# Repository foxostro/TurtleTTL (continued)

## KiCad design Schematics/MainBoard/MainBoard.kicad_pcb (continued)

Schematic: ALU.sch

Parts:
C74, C75, C76, C77: 100nF; C_Disc_D4.3mm_W1.9mm_P5.00mm
D3, D4: LED; LED_D5.0mm
J10: ALU Result LED Connector; PinSocket_1x09_P2.54mm_Vertical
R28, R29: 220Ω; R_Axial_DIN0207_L6.3mm_D2.5mm_P7.62mm_Horizontal
R38: 4.7kΩ; R_Axial_DIN0207_L6.3mm_D2.5mm_P7.62mm_Horizontal
U69, U70: 74F181; DIP-24_W15.24mm_Socket
U71: 74LS245; DIP-20_W7.62mm_Socket
U72: 74F377; DIP-20_W7.62mm

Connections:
/ALU/A=B: R38.2, U69.14 (A=B), U70.14 (A=B), U72.4 (D1)
/ALU/AluResult0: J10.2, U69.9 (F0), U71.2 (A0)
/ALU/AluResult1: J10.3, U69.10 (F1), U71.3 (A1)
/ALU/AluResult2: J10.4, U69.11 (F2), U71.4 (A2)
/ALU/AluResult3: J10.5, U69.13 (F3), U71.5 (A3)
/ALU/AluResult4: J10.6, U70.9 (F0), U71.6 (A4)
/ALU/AluResult5: J10.7, U70.10 (F1), U71.7 (A5)
/ALU/AluResult6: J10.8, U70.11 (F2), U71.8 (A6)
/ALU/AluResult7: J10.9, U70.13 (F3), U71.9 (A7)
/ALU/Cn+4: U70.16 (Cn+4), U72.3 (D0)
A0: U69.2 (A0); also elsewhere on the board
A1: U69.23 (A1); also elsewhere on the board
A2: U69.21 (A2); also elsewhere on the board
A3: U69.19 (A3); also elsewhere on the board
A4: U70.2 (A0); also elsewhere on the board
A5: U70.23 (A1); also elsewhere on the board
A6: U70.21 (A2); also elsewhere on the board
A7: U70.19 (A3); also elsewhere on the board
B0: U69.1 (B0); also elsewhere on the board
B1: U69.22 (B1); also elsewhere on the board
B2: U69.20 (B2); also elsewhere on the board
B3: U69.18 (B3); also elsewhere on the board
B4: U70.1 (B0); also elsewhere on the board
B5: U70.22 (B1); also elsewhere on the board
B6: U70.20 (B2); also elsewhere on the board
B7: U70.18 (B3); also elsewhere on the board
C0: U69.6 (S0), U70.6 (S0); also elsewhere on the board
C1: U69.5 (S1), U70.5 (S1); also elsewhere on the board
C2: U69.4 (S2), U70.4 (S2); also elsewhere on the board
C3: U69.3 (S3), U70.3 (S3); also elsewhere on the board
C4: U69.7 (Cn); also elsewhere on the board
C5: U69.8 (M), U70.8 (M); also elsewhere on the board
DataBus0: U71.18 (B0); also elsewhere on the board
DataBus1: U71.17 (B1); also elsewhere on the board
DataBus2: U71.16 (B2); also elsewhere on the board
DataBus3: U71.15 (B3); also elsewhere on the board
DataBus4: U71.14 (B4); also elsewhere on the board
DataBus5: U71.13 (B5); also elsewhere on the board
DataBus6: U71.12 (B6); also elsewhere on the board
DataBus7: U71.11 (B7); also elsewhere on the board
GND: C74.2, C75.2, C76.2, C77.2, J10.1, R28.2, R29.2, U69.12 (GND), U70.12 (GND), U71.10 (GND), U72.10 (GND); also elsewhere on the board
unnamed: D3.1 (K), R28.1
unnamed: D4.1 (K), R29.1
unnamed: U69.16 (Cn+4), U70.7 (Cn)
RegisterClock: U72.11 (CP); also elsewhere on the board
VCC: C74.1, C75.1, C76.1, C77.1, R38.1, U69.24 (VCC), U70.24 (VCC), U71.1 (A->B), U71.20 (VCC), U72.20 (VCC); also elsewhere on the board
~A=B: D4.2 (A), U72.5 (Q1); also elsewhere on the board
~CarryOut: D3.2 (A), U72.2 (Q0); also elsewhere on the board
~EO: U71.19 (CE); also elsewhere on the board
~FI: U72.1 (~E); also elsewhere on the board

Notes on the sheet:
Flags Register

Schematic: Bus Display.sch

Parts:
J11: Address Bus LED Connector; PinSocket_1x17_P2.54mm_Vertical
J12: Data Bus LED Connector; PinSocket_1x09_P2.54mm_Vertical
RN1: 1kΩ; R_Array_SIP9

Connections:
AddressBus0: J11.2; also elsewhere on the board
AddressBus1: J11.3; also elsewhere on the board
AddressBus2: J11.4; also elsewhere on the board
AddressBus3: J11.5; also elsewhere on the board
AddressBus4: J11.6; also elsewhere on the board
AddressBus5: J11.7; also elsewhere on the board
AddressBus6: J11.8; also elsewhere on the board
AddressBus7: J11.9; also elsewhere on the board
AddressBus8: J11.10; also elsewhere on the board
AddressBus9: J11.11; also elsewhere on the board
AddressBus10: J11.12; also elsewhere on the board
AddressBus11: J11.13; also elsewhere on the board
AddressBus12: J11.14; also elsewhere on the board
AddressBus13: J11.15; also elsewhere on the board
AddressBus14: J11.16; also elsewhere on the board
AddressBus15: J11.17; also elsewhere on the board
DataBus0: J12.2, RN1.2 (R1); also elsewhere on the board
DataBus1: J12.3, RN1.3 (R2); also elsewhere on the board
DataBus2: J12.4, RN1.4 (R3); also elsewhere on the board
DataBus3: J12.5, RN1.5 (R4); also elsewhere on the board
DataBus4: J12.6, RN1.6 (R5); also elsewhere on the board
DataBus5: J12.7, RN1.7 (R6); also elsewhere on the board
DataBus6: J12.8, RN1.8 (R7); also elsewhere on the board
DataBus7: J12.9, RN1.9 (R8); also elsewhere on the board
GND: J11.1, J12.1, RN1.1 (common); also elsewhere on the board

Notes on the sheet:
Data Bus Pull-down Resistors

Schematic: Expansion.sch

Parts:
J17: Device 2; PinSocket_2x20_P2.54mm_Vertical
J18: Device 5; PinSocket_2x20_P2.54mm_Vertical
J19: Device 3; PinSocket_2x20_P2.54mm_Vertical
J20: Device 6; PinSocket_2x20_P2.54mm_Vertical
J21: Device 4; PinSocket_2x20_P2.54mm_Vertical
J22: Device 7; PinSocket_2x20_P2.54mm_Vertical

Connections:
AddressBus0: J17.3, J18.3, J19.3, J20.3, J21.3, J22.3; also elsewhere on the board
AddressBus1: J17.4, J18.4, J19.4, J20.4, J21.4, J22.4; also elsewhere on the board
AddressBus2: J17.5, J18.5, J19.5, J20.5, J21.5, J22.5; also elsewhere on the board
AddressBus3: J17.6, J18.6, J19.6, J20.6, J21.6, J22.6; also elsewhere on the board
AddressBus4: J17.7, J18.7, J19.7, J20.7, J21.7, J22.7; also elsewhere on the board
AddressBus5: J17.8, J18.8, J19.8, J20.8, J21.8, J22.8; also elsewhere on the board
AddressBus6: J17.9, J18.9, J19.9, J20.9, J21.9, J22.9; also elsewhere on the board
AddressBus7: J17.10, J18.10, J19.10, J20.10, J21.10, J22.10; also elsewhere on the board
AddressBus8: J17.11, J18.11, J19.11, J20.11, J21.11, J22.11; also elsewhere on the board
AddressBus9: J17.12, J18.12, J19.12, J20.12, J21.12, J22.12; also elsewhere on the board
AddressBus10: J17.13, J18.13, J19.13, J20.13, J21.13, J22.13; also elsewhere on the board
AddressBus11: J17.14, J18.14, J19.14, J20.14, J21.14, J22.14; also elsewhere on the board
AddressBus12: J17.15, J18.15, J19.15, J20.15, J21.15, J22.15; also elsewhere on the board
AddressBus13: J17.16, J18.16, J19.16, J20.16, J21.16, J22.16; also elsewhere on the board
AddressBus14: J17.17, J18.17, J19.17, J20.17, J21.17, J22.17; also elsewhere on the board
AddressBus15: J17.18, J18.18, J19.18, J20.18, J21.18, J22.18; also elsewhere on the board
DataBus0: J17.21, J18.21, J19.21, J20.21, J21.21, J22.21; also elsewhere on the board
DataBus1: J17.22, J18.22, J19.22, J20.22, J21.22, J22.22; also elsewhere on the board
DataBus2: J17.23, J18.23, J19.23, J20.23, J21.23, J22.23; also elsewhere on the board
DataBus3: J17.24, J18.24, J19.24, J20.24, J21.24, J22.24; also elsewhere on the board
DataBus4: J17.25, J18.25, J19.25, J20.25, J21.25, J22.25; also elsewhere on the board
DataBus5: J17.26, J18.26, J19.26, J20.26, J21.26, J22.26; also elsewhere on the board
DataBus6: J17.27, J18.27, J19.27, J20.27, J21.27, J22.27; also elsewhere on the board
DataBus7: J17.28, J18.28, J19.28, J20.28, J21.28, J22.28; also elsewhere on the board
FixedRateClock: J17.20, J18.20, J19.20, J20.20, J21.20, J22.20; also elsewhere on the board
GND: J17.1, J17.31, J17.32, J17.33, J17.34, J17.35, J17.36, J17.37, J17.38, J17.39, J17.40, J18.1, J18.31, J18.32, J18.33, J18.34, J18.35, J18.36, J18.37, J18.38, J18.39, J18.40, J19.1, J19.31, J19.32, J19.33, J19.34, J19.35, J19.36, J19.37, J19.38, J19.39, J19.40, J20.1, J20.31, J20.32, J20.33, J20.34, J20.35, J20.36, J20.37, J20.38, J20.39, J20.40, J21.1, J21.31, J21.32, J21.33, J21.34, J21.35, J21.36, J21.37, J21.38, J21.39, J21.40, J22.1, J22.31, J22.32, J22.33, J22.34, J22.35, J22.36, J22.37, J22.38, J22.39, J22.40; also elsewhere on the board
RegisterClock: J17.19, J18.19, J19.19, J20.19, J21.19, J22.19; also elsewhere on the board
VCC: J17.2, J18.2, J19.2, J20.2, J21.2, J22.2; also elsewhere on the board
~PI2: J17.29; also elsewhere on the board
~PI3: J19.29; also elsewhere on the board
~PI4: J21.29; also elsewhere on the board
~PI5: J18.29; also elsewhere on the board
~PI6: J20.29; also elsewhere on the board
~PI7: J22.29; also elsewhere on the board
~PO2: J17.30; also elsewhere on the board
~PO3: J19.30; also elsewhere on the board
~PO4: J21.30; also elsewhere on the board
~PO5: J18.30; also elsewhere on the board
~PO6: J20.30; also elsewhere on the board
~PO7: J22.30; also elsewhere on the board

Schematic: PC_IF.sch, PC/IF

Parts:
C22, C23: 100nF; C_Disc_D4.3mm_W1.9mm_P5.00mm
U22, U23: 74F574; DIP-20_W7.62mm

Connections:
ControlClock: U22.11 (Cp), U23.11 (Cp); also elsewhere on the board
GND: C22.2, C23.2, U22.1 (OE), U22.10 (GND), U23.1 (OE), U23.10 (GND); also elsewhere on the board
PC0: U22.2 (D0); also elsewhere on the board
PC1: U22.3 (D1); also elsewhere on the board
PC2: U22.4 (D2); also elsewhere on the board
PC3: U22.5 (D3); also elsewhere on the board
PC4: U22.6 (D4); also elsewhere on the board
PC5: U22.7 (D5); also elsewhere on the board
PC6: U22.8 (D6); also elsewhere on the board
PC7: U22.9 (D7); also elsewhere on the board
PC8: U23.2 (D0); also elsewhere on the board
PC9: U23.3 (D1); also elsewhere on the board
PC10: U23.4 (D2); also elsewhere on the board
PC11: U23.5 (D3); also elsewhere on the board
PC12: U23.6 (D4); also elsewhere on the board
PC13: U23.7 (D5); also elsewhere on the board
PC14: U23.8 (D6); also elsewhere on the board
PC15: U23.9 (D7); also elsewhere on the board
PC_IF0: U22.19 (Q0); also elsewhere on the board
PC_IF1: U22.18 (Q1); also elsewhere on the board
PC_IF2: U22.17 (Q2); also elsewhere on the board
PC_IF3: U22.16 (Q3); also elsewhere on the board
PC_IF4: U22.15 (Q4); also elsewhere on the board
PC_IF5: U22.14 (Q5); also elsewhere on the board
PC_IF6: U22.13 (Q6); also elsewhere on the board
PC_IF7: U22.12 (Q7); also elsewhere on the board
PC_IF8: U23.19 (Q0); also elsewhere on the board
PC_IF9: U23.18 (Q1); also elsewhere on the board
PC_IF10: U23.17 (Q2); also elsewhere on the board
PC_IF11: U23.16 (Q3); also elsewhere on the board
PC_IF12: U23.15 (Q4); also elsewhere on the board
PC_IF13: U23.14 (Q5); also elsewhere on the board
PC_IF14: U23.13 (Q6); also elsewhere on the board
PC_IF15: U23.12 (Q7); also elsewhere on the board
VCC: C22.1, C23.1, U22.20 (VCC), U23.20 (VCC); also elsewhere on the board

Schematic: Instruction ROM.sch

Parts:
J13: PC/IF Connector [0..7]; PinSocket_1x09_P2.54mm_Vertical
J14: PC/IF Connector [8..15]; PinSocket_1x09_P2.54mm_Vertical
J15: IROM Connector [0..7]; PinSocket_1x08_P2.54mm_Vertical
J16: IROM Connector [8..15]; PinSocket_1x08_P2.54mm_Vertical

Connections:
GND: J14.1; also elsewhere on the board
IROM0: J15.1; also elsewhere on the board
IROM1: J15.2; also elsewhere on the board
IROM2: J15.3; also elsewhere on the board
IROM3: J15.4; also elsewhere on the board
IROM4: J15.5; also elsewhere on the board
IROM5: J15.6; also elsewhere on the board
IROM6: J15.7; also elsewhere on the board
IROM7: J15.8; also elsewhere on the board
IROM8: J16.1; also elsewhere on the board
IROM9: J16.2; also elsewhere on the board
IROM10: J16.3; also elsewhere on the board
IROM11: J16.4; also elsewhere on the board
IROM12: J16.5; also elsewhere on the board
IROM13: J16.6; also elsewhere on the board
IROM14: J16.7; also elsewhere on the board
IROM15: J16.8; also elsewhere on the board
PC_IF0: J13.2; also elsewhere on the board
PC_IF1: J13.3; also elsewhere on the board
PC_IF2: J13.4; also elsewhere on the board
PC_IF3: J13.5; also elsewhere on the board
PC_IF4: J13.6; also elsewhere on the board
PC_IF5: J13.7; also elsewhere on the board
PC_IF6: J13.8; also elsewhere on the board
PC_IF7: J13.9; also elsewhere on the board
PC_IF8: J14.2; also elsewhere on the board
PC_IF9: J14.3; also elsewhere on the board
PC_IF10: J14.4; also elsewhere on the board
PC_IF11: J14.5; also elsewhere on the board
PC_IF12: J14.6; also elsewhere on the board
PC_IF13: J14.7; also elsewhere on the board
PC_IF14: J14.8; also elsewhere on the board
PC_IF15: J14.9; also elsewhere on the board
VCC: J13.1; also elsewhere on the board

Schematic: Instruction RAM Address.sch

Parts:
C26, C27, C28, C29: 100nF; C_Disc_D4.3mm_W1.9mm_P5.00mm
U26, U27, U28, U29: 74F157; DIP-16_W7.62mm

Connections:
AddressBus0: U26.3 (I1a); also elsewhere on the board
AddressBus1: U26.6 (I1b); also elsewhere on the board
AddressBus2: U26.13 (I1d); also elsewhere on the board
AddressBus3: U26.10 (I1c); also elsewhere on the board
AddressBus4: U27.3 (I1a); also elsewhere on the board
AddressBus5: U27.6 (I1b); also elsewhere on the board
AddressBus6: U27.13 (I1d); also elsewhere on the board
AddressBus7: U27.10 (I1c); also elsewhere on the board
AddressBus8: U28.3 (I1a); also elsewhere on the board
AddressBus9: U28.6 (I1b); also elsewhere on the board
AddressBus10: U28.13 (I1d); also elsewhere on the board
AddressBus11: U28.10 (I1c); also elsewhere on the board
AddressBus12: U29.3 (I1a); also elsewhere on the board
AddressBus13: U29.6 (I1b); also elsewhere on the board
AddressBus14: U29.13 (I1d); also elsewhere on the board
AddressBus15: U29.10 (I1c); also elsewhere on the board
GND: C26.2, C27.2, C28.2, C29.2, U26.8 (GND), U26.15 (E), U27.8 (GND), U27.15 (E), U28.8 (GND), U28.15 (E), U29.8 (GND), U29.15 (E); also elsewhere on the board
IRAMAddr0: U26.4 (Za); also elsewhere on the board
IRAMAddr1: U26.7 (Zb); also elsewhere on the board
IRAMAddr2: U26.12 (Zd); also elsewhere on the board
IRAMAddr3: U26.9 (Zc); also elsewhere on the board
IRAMAddr4: U27.4 (Za); also elsewhere on the board
IRAMAddr5: U27.7 (Zb); also elsewhere on the board
IRAMAddr6: U27.12 (Zd); also elsewhere on the board
IRAMAddr7: U27.9 (Zc); also elsewhere on the board
IRAMAddr8: U28.4 (Za); also elsewhere on the board
IRAMAddr9: U28.7 (Zb); also elsewhere on the board
IRAMAddr10: U28.12 (Zd); also elsewhere on the board
IRAMAddr11: U28.9 (Zc); also elsewhere on the board
IRAMAddr12: U29.4 (Za); also elsewhere on the board
IRAMAddr13: U29.7 (Zb); also elsewhere on the board
IRAMAddr14: U29.12 (Zd); also elsewhere on the board
PC_IF0: U26.2 (I0a); also elsewhere on the board
PC_IF1: U26.5 (I0b); also elsewhere on the board
PC_IF2: U26.14 (I0d); also elsewhere on the board
PC_IF3: U26.11 (I0c); also elsewhere on the board
PC_IF4: U27.2 (I0a); also elsewhere on the board
PC_IF5: U27.5 (I0b); also elsewhere on the board
PC_IF6: U27.14 (I0d); also elsewhere on the board
PC_IF7: U27.11 (I0c); also elsewhere on the board
PC_IF8: U28.2 (I0a); also elsewhere on the board
PC_IF9: U28.5 (I0b); also elsewhere on the board
PC_IF10: U28.14 (I0d); also elsewhere on the board
PC_IF11: U28.11 (I0c); also elsewhere on the board
PC_IF12: U29.2 (I0a); also elsewhere on the board
PC_IF13: U29.5 (I0b); also elsewhere on the board
PC_IF14: U29.14 (I0d); also elsewhere on the board
PC_IF15: U26.1 (S), U27.1 (S), U28.1 (S), U29.1 (S), U29.11 (I0c); also elsewhere on the board
VCC: C26.1, C27.1, C28.1, C29.1, U26.16 (VCC), U27.16 (VCC), U28.16 (VCC), U29.16 (VCC); also elsewhere on the board

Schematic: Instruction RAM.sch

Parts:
C30, C31, C32, C33, C34, C35: 100nF; C_Disc_D4.3mm_W1.9mm_P5.00mm
U30: 74LS08; DIP-14_W7.62mm
U31: 74LS04; DIP-14_W7.62mm
U33, U34: IDT71256SA12TPG; DIP-28_W7.62mm_Socket
U35, U36: 74LS245; DIP-20_W7.62mm_Socket

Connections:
DataBus0: U35.18 (B0), U36.18 (B0); also elsewhere on the board
DataBus1: U35.17 (B1), U36.17 (B1); also elsewhere on the board
DataBus2: U35.16 (B2), U36.16 (B2); also elsewhere on the board
DataBus3: U35.15 (B3), U36.15 (B3); also elsewhere on the board
DataBus4: U35.14 (B4), U36.14 (B4); also elsewhere on the board
DataBus5: U35.13 (B5), U36.13 (B5); also elsewhere on the board
DataBus6: U35.12 (B6), U36.12 (B6); also elsewhere on the board
DataBus7: U35.11 (B7), U36.11 (B7); also elsewhere on the board
GND: C30.2, C31.2, C32.2, C33.2, C34.2, C35.2, U33.14 (GND), U33.20 (~CS), U34.14 (GND), U34.20 (~CS), U35.10 (GND), U36.10 (GND); also elsewhere on the board
IRAM0: U34.11 (D0), U36.2 (A0); also elsewhere on the board
IRAM1: U34.12 (D1), U36.3 (A1); also elsewhere on the board
IRAM2: U34.13 (D2), U36.4 (A2); also elsewhere on the board
IRAM3: U34.15 (D3), U36.5 (A3); also elsewhere on the board
IRAM4: U34.16 (D4), U36.6 (A4); also elsewhere on the board
IRAM5: U34.17 (D5), U36.7 (A5); also elsewhere on the board
IRAM6: U34.18 (D6), U36.8 (A6); also elsewhere on the board
IRAM7: U34.19 (D7), U36.9 (A7); also elsewhere on the board
IRAM8: U33.11 (D0), U35.2 (A0); also elsewhere on the board
IRAM9: U33.12 (D1), U35.3 (A1); also elsewhere on the board
IRAM10: U33.13 (D2), U35.4 (A2); also elsewhere on the board
IRAM11: U33.15 (D3), U35.5 (A3); also elsewhere on the board
IRAM12: U33.16 (D4), U35.6 (A4); also elsewhere on the board
IRAM13: U33.17 (D5), U35.7 (A5); also elsewhere on the board
IRAM14: U33.18 (D6), U35.8 (A6); also elsewhere on the board
IRAM15: U33.19 (D7), U35.9 (A7); also elsewhere on the board
IRAMAddr0: U33.10 (A0), U34.10 (A0); also elsewhere on the board
IRAMAddr1: U33.9 (A1), U34.9 (A1); also elsewhere on the board
IRAMAddr2: U33.8 (A2), U34.8 (A2); also elsewhere on the board
IRAMAddr3: U33.7 (A3), U34.7 (A3); also elsewhere on the board
IRAMAddr4: U33.6 (A4), U34.6 (A4); also elsewhere on the board
IRAMAddr5: U33.5 (A5), U34.5 (A5); also elsewhere on the board
IRAMAddr6: U33.4 (A6), U34.4 (A6); also elsewhere on the board
IRAMAddr7: U33.3 (A7), U34.3 (A7); also elsewhere on the board
IRAMAddr8: U33.25 (A8), U34.25 (A8); also elsewhere on the board
IRAMAddr9: U33.24 (A9), U34.24 (A9); also elsewhere on the board
IRAMAddr10: U33.21 (A10), U34.21 (A10); also elsewhere on the board
IRAMAddr11: U33.23 (A11), U34.23 (A11); also elsewhere on the board
IRAMAddr12: U33.2 (A12), U34.2 (A12); also elsewhere on the board
IRAMAddr13: U33.26 (A13), U34.26 (A13); also elsewhere on the board
IRAMAddr14: U33.1 (A14), U34.1 (A14); also elsewhere on the board
unnamed: U30.3, U35.19 (CE)
unnamed: U30.6, U36.19 (CE)
unnamed: U31.2, U33.22 (~OE)
unnamed: U31.4, U34.22 (~OE)
VCC: C30.1, C31.1, C32.1, C33.1, C34.1, C35.1, U33.28 (VCC), U34.28 (VCC), U35.20 (VCC), U36.20 (VCC); also elsewhere on the board
~PI0: U30.2, U31.1, U33.27 (~WE), U35.1 (A->B); also elsewhere on the board
~PI1: U30.5, U31.3, U34.27 (~WE), U36.1 (A->B); also elsewhere on the board
~PO0: U30.1; also elsewhere on the board
~PO1: U30.4; also elsewhere on the board

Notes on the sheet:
For purposes of reading and writing, Instruction RAM is mapped to both the lower and upper halves of the address space. Though, the control unit only executes code in the upper half.
Programs must take care to never read or write to Instruction RAM while the program counter is in the upper half of the address space. This will surely lead to unexpected and incorrect operation.

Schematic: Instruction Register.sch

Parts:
C37, C38, C39, C40, C41, C42: 100nF; C_Disc_D4.3mm_W1.9mm_P5.00mm
J4: Instruction Register LED Connector; PinSocket_1x17_P2.54mm_Vertical
U37, U38, U40, U41: 74F157; DIP-16_W7.62mm
U39, U42: 74F574; DIP-20_W7.62mm

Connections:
ControlClock: U39.11 (Cp), U42.11 (Cp); also elsewhere on the board
GND: C37.2, C38.2, C39.2, C40.2, C41.2, C42.2, J4.1, U37.8 (GND), U37.15 (E), U38.8 (GND), U38.15 (E), U39.1 (OE), U39.10 (GND), U40.8 (GND), U40.15 (E), U41.8 (GND), U41.15 (E), U42.1 (OE), U42.10 (GND); also elsewhere on the board
IR0: J4.2, U39.19 (Q0); also elsewhere on the board
IR1: J4.3, U39.18 (Q1); also elsewhere on the board
IR2: J4.4, U39.17 (Q2); also elsewhere on the board
IR3: J4.5, U39.16 (Q3); also elsewhere on the board
IR4: J4.6, U39.15 (Q4); also elsewhere on the board
IR5: J4.7, U39.14 (Q5); also elsewhere on the board
IR6: J4.8, U39.13 (Q6); also elsewhere on the board
IR7: J4.9, U39.12 (Q7); also elsewhere on the board
IR8: J4.10, U42.19 (Q0); also elsewhere on the board
IR9: J4.11, U42.18 (Q1); also elsewhere on the board
IR10: J4.12, U42.17 (Q2); also elsewhere on the board
IR11: J4.13, U42.16 (Q3); also elsewhere on the board
IR12: J4.14, U42.15 (Q4); also elsewhere on the board
IR13: J4.15, U42.14 (Q5); also elsewhere on the board
IR14: J4.16, U42.13 (Q6); also elsewhere on the board
IR15: J4.17, U42.12 (Q7); also elsewhere on the board
IRAM0: U37.3 (I1a); also elsewhere on the board
IRAM1: U37.6 (I1b); also elsewhere on the board
IRAM2: U37.10 (I1c); also elsewhere on the board
IRAM3: U37.13 (I1d); also elsewhere on the board
IRAM4: U38.3 (I1a); also elsewhere on the board
IRAM5: U38.6 (I1b); also elsewhere on the board
IRAM6: U38.10 (I1c); also elsewhere on the board
IRAM7: U38.13 (I1d); also elsewhere on the board
IRAM8: U40.3 (I1a); also elsewhere on the board
IRAM9: U40.6 (I1b); also elsewhere on the board
IRAM10: U40.10 (I1c); also elsewhere on the board
IRAM11: U40.13 (I1d); also elsewhere on the board
IRAM12: U41.3 (I1a); also elsewhere on the board
IRAM13: U41.6 (I1b); also elsewhere on the board
IRAM14: U41.10 (I1c); also elsewhere on the board
IRAM15: U41.13 (I1d); also elsewhere on the board
IROM0: U37.2 (I0a); also elsewhere on the board
IROM1: U37.5 (I0b); also elsewhere on the board
IROM2: U37.11 (I0c); also elsewhere on the board
IROM3: U37.14 (I0d); also elsewhere on the board
IROM4: U38.2 (I0a); also elsewhere on the board
IROM5: U38.5 (I0b); also elsewhere on the board
IROM6: U38.11 (I0c); also elsewhere on the board
IROM7: U38.14 (I0d); also elsewhere on the board
IROM8: U40.2 (I0a); also elsewhere on the board
IROM9: U40.5 (I0b); also elsewhere on the board
IROM10: U40.11 (I0c); also elsewhere on the board
IROM11: U40.14 (I0d); also elsewhere on the board
IROM12: U41.2 (I0a); also elsewhere on the board
IROM13: U41.5 (I0b); also elsewhere on the board
IROM14: U41.11 (I0c); also elsewhere on the board
IROM15: U41.14 (I0d); also elsewhere on the board
unnamed: U37.4 (Za), U39.2 (D0)
unnamed: U37.7 (Zb), U39.3 (D1)
unnamed: U37.9 (Zc), U39.4 (D2)
unnamed: U37.12 (Zd), U39.5 (D3)
unnamed: U38.4 (Za), U39.6 (D4)
unnamed: U38.7 (Zb), U39.7 (D5)
unnamed: U38.9 (Zc), U39.8 (D6)
unnamed: U38.12 (Zd), U39.9 (D7)
unnamed: U40.4 (Za), U42.2 (D0)
unnamed: U40.7 (Zb), U42.3 (D1)
unnamed: U40.9 (Zc), U42.4 (D2)
unnamed: U40.12 (Zd), U42.5 (D3)
unnamed: U41.4 (Za), U42.6 (D4)
unnamed: U41.7 (Zb), U42.7 (D5)
unnamed: U41.9 (Zc), U42.8 (D6)
unnamed: U41.12 (Zd), U42.9 (D7)
PC15: U37.1 (S), U38.1 (S), U40.1 (S), U41.1 (S); also elsewhere on the board
VCC: C37.1, C38.1, C39.1, C40.1, C41.1, C42.1, U37.16 (VCC), U38.16 (VCC), U39.20 (VCC), U40.16 (VCC), U41.16 (VCC), U42.20 (VCC); also elsewhere on the board

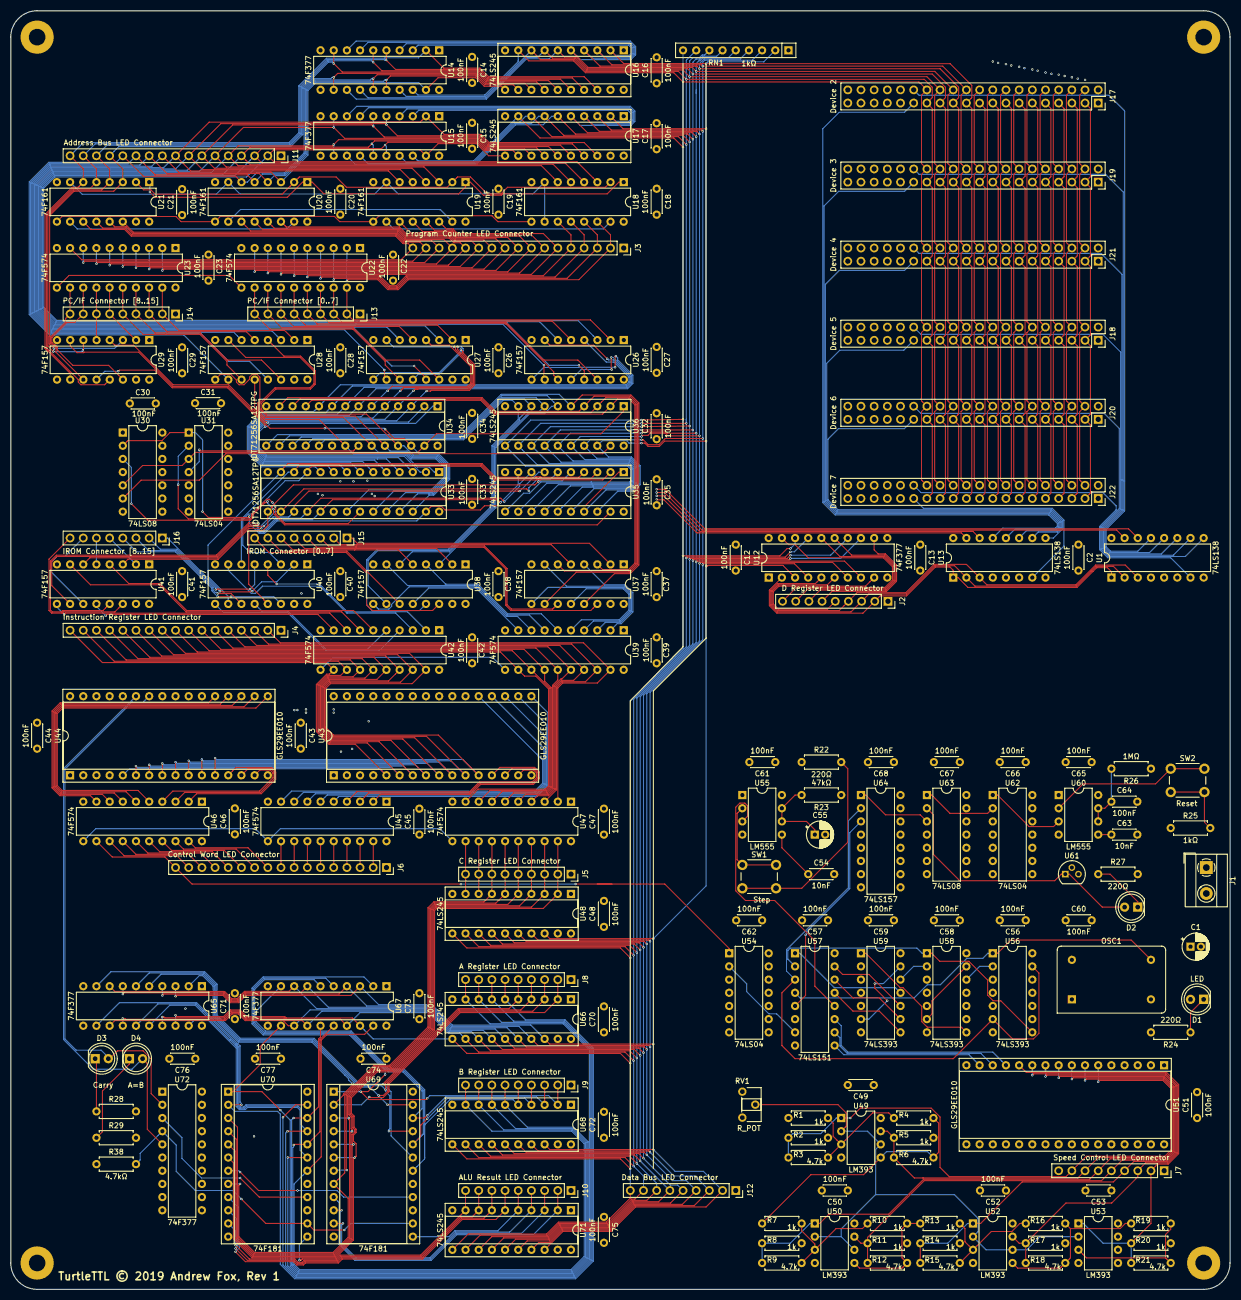
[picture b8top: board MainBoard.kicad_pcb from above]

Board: 6 copper layers, 234.9 x 246.4 mm, 188 parts (0 on the bottom side), 286 nets.

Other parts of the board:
C2: 100nF; C_Disc_D4.3mm_W1.9mm_P5.00mm
OSC1: 10MHz; Oscillator_DIP-14
U1: 74LS138; DIP-16_W7.62mm

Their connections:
D0: U1.1; also elsewhere on the board
D1: U1.2; also elsewhere on the board
D2: U1.3; also elsewhere on the board
GND: C2.2, OSC1.7, U1.8; also elsewhere on the board
unnamed 152: OSC1.8; also elsewhere on the board
VCC: C2.1, OSC1.14, U1.6, U1.16; also elsewhere on the board
~PO: U1.4, U1.5; also elsewhere on the board
~PO0: U1.15; also elsewhere on the board
~PO1: U1.14; also elsewhere on the board
~PO2: U1.13; also elsewhere on the board
~PO3: U1.12; also elsewhere on the board
~PO4: U1.11; also elsewhere on the board
~PO5: U1.10; also elsewhere on the board
~PO6: U1.9; also elsewhere on the board
~PO7: U1.7; also elsewhere on the board

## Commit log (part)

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2020-06-30 Add LT16 instruction to the IR.
2020-07-01 Added STORE16, LOAD16, LT16, and GE16 instructions to the IR.
2020-07-01 Use sixteen-bit math to compute local variable addresses.
    Also, settle on a convention: everything is big endian. I wasn't super
    consistent about this previously.
2020-07-03 Literal int expressions can compile sixteen-bit values.
2020-07-04 Functions can return u16 too now.
2020-07-06 Pop arguments off the stack when a function call returns
2020-07-09 Add more unit tests for EQ and EQ16
2020-07-09 Add more tests for GE and GE16
2020-07-09 Add more tests for DIV and DIV16
2020-07-09 Fix unit test for mutually recursive function. Test was wrong.
2020-07-09 Add the ability to declare a variable with an explicit type.
    BUG: There's no type checking that the expression type is convertible to
    the explicit symbol type.
2020-07-11 Refactor: use pattern matching switch in SnapToYertleCompiler
2020-07-12 Sound card: Start assigning SMD footprints to schematic components.
2020-07-19 Sound Card: Add 3D render of the sound card
2020-07-26 Can assign valies to array elements through the subscript operator.
    The compiler now has a concept of lvalue and rvalue expressions.
2020-07-26 Array expression statements will pop the stack when complete.
    Expression statements must not make stack changes that persist past the end
    of the statement.
    Added a new IR instruction POPN which pops an arbitrary number of words.
2020-07-26 The type of an array literal can be automatically converted on initial assignment.
    This allows array literals like [1, 2, 3] to be assigned to a [u16] by
    informing the compiler that it needs to generate u16 values.
2020-07-26 Arrays may be returned from functions.
    Function return values are passed on the stack.
2020-07-26 The parser can now parse arrays.
    TODO: Arrays in expressions do not compile correctly.
2020-07-26 Add a unit test for Snap which prints "Hello, World!" to the serial interface.
2020-07-29 Add unit test to demonstrate evaluation of dynamic array identifier.
    A dynamic array consists of a pointer and a count. Evaluating a symbol of
    a dynamic array type results in these two values being pushed to the stack.
2020-07-29 The parser parses types like `[]T' as dynamic array types.
2020-07-30 Added hlt(), a compiler intrinsic function to halt the computer.
2020-08-01 The compiler prints out the offending line and highlights the error.
2020-08-03 Compiler generates temporary labels with new class LabelMaker.
2020-08-03 Array OOB errors call a special stdlib panic function now.
    For this function, YertleExecutor uses a test stub.
    SnapExecutor gets the actual function from the stdlib, but only is a flag
    is set. Programs which use arrays will always need the stdlib.
2020-08-05 Rename IR language classes.
    Remove fun, whimsical names and replace with utilitarian names.
2020-08-11 Add Three-Address Code versions of eight-bit comparison instructions.
2020-08-11 Add Three-Address Code style instruction for GT16
2020-08-15 LvalueExpressionCompilerTests all pass now, using TAC-style instructions
2020-08-25 CrackleExecutor disassembly uses the instruction's description method now
2020-08-25 Fix tests testDynamicArraySubscriptAccessesAnArrayElement_{U8,U16,Bool}
2020-08-25 dynamicArrayBoundsCheck uses fewer temporaries now
2020-08-26 Fix unit tests for getting array count.
    Fix the following tests:
    * testGetLengthOfLiteralArray
    * testGetLengthOfArrayThroughIdentifier
    * testGetLengthOfDynamicArray
    When getting the count of an array, first evaluate the array expression
    and allow the result to be written to a temporary. (This is necesary in
2020-08-27 add some comments about why bits of code are effectively unreachable
2020-08-28 Add tests in RvalueExpressionCompilerTest for compiler intrinsic functions.
2020-08-29 Refactor: extract code to compile each of the the compiler intrinsic functions
2020-08-31 Fix unit test test_EndToEndIntegration_AccessVariableInFunction_U16
    The function which emits code to compute a local variable address needed
    to be able to handle the case where offset<0. Also, the code emitted to
    save/restore temporaries around a function call was incorrect.
2020-09-01 Fix compilation of if-statement to use the new three-address code IR.
2020-09-02 Add new test testUnexpectedNonVoidReturnValueInVoidFunction to SnapToCrackleCompilerTests
    This tests the case where a function returns a value when it should not.
2020-09-02 Fix bug where conversion from u16 to u8 was copying the high byte when we expected the low byte.
2020-09-02 Fix CompilerTemporariesAllocatorTests which was broken by a recent change which rounds temporaries up to multiples of two bytes.
2020-09-03 Add a new IR instruction SUBSP which subtracts from the stack pointer.
2020-09-04 Rename three-address code instructions to remove "tac_" prefix.
2020-09-04 Main Board: Fix the reset LED by buffering with an inverter.
2020-09-06 Added a `struct' token
2020-09-07 AST nodes specify types through expressions which evaluates to types.
2020-09-11 Can now get the Lvalue of a struct field too.
2020-09-13 Avoid creating a temporary struct when assigning via initializer.
    When assigning to a struct via a struct initializer expression, it is not
    necessary to create an entire temporary struct and then copy that struct
    into the destination. Instead, compile and assign each member separately.
2020-09-13 Add Twinkle Twinkle Little Star example program, written in Snap.
2020-09-15 Plug the hole in the type system relating to pointers and mutability.
    Do not introduce a `const' keyword as this introduces a lot of complexity
    into the language and type system. Instead, mutable pointers are able to
    mutate the pointee, and immutable pointers are not able. While this lacks
    some of the expressiveness afforded by adding `const' versions of types,
    it is much simpler.
2020-09-16 Refactor: avoid listing all combinations of types for a binary expression.
    Instead of listing all combinations explicitly, use some logic to compress
    things down to a smaller number of cases.
2020-09-16 Add a type for "const bool". Rules for constness have not been implemented.
2020-09-16 Remove shouldIgnoreMutabilityRules from LvalueExpressionCompiler.
    Enforcement of mutability rules is to be done in the
    RvalueExpressionTypeChecker when it checks the Assignment expression.
2020-09-17 Fix broken unit tests related to pointer type conversions with a const pointee.
2020-09-19 Update Xcode project deployment target and settings.
2020-09-19 add syntax for a for-range loop which parses to a while-loop
2020-09-19 For-in style loop can iterate over a dynamic array too.
2020-09-21 Struct types can include a pointer to an element of the same type.
2020-09-22 Add typealias statement
2020-09-24 Fix bug where function could not return a const value.
    Attempting to do so would raise an error about not being able to assign to
    the constant __return.
2020-09-25 Add a MULI16 instruction and use it in arrayBoundsCheck().
    This instructions multiplies an operand by an immediate value.
2020-09-26 Only public types are exported from modules now. No syntax for declaring it
    Symbols and types now have a visibility and only public types are exported
    from modules. Though, there is no syntax to declare a type as public or
    private in code yet. This is only used to prevent types from being exported
    transitively.
2020-09-27 Can inject module text into the compiler so we can test import statements.
2020-10-04 Added compiler support for an assert statement.
2020-10-10 Remove extraneous newline from command line tool error output.
2020-10-12 Added syntax for the import statement.
    Import a module from file with the import statement.
2020-10-15 Add IR instruction to copy the address of a label to memory.
2020-10-15 A function pointer can be rebound at run time.
    When making a function call through a function pointer, evaluate the
    callee expression to determine the function address and then branch to
    that address.
2020-10-16 Rename the parameters of Expression.Subscript from identifier/expr to subscriptable/argument
2020-10-16 Fix bug which broke code that tried to get a dynamic array from a struct and subscript it.
    The compiler no longer assumes the subscriptable expression is a simple
    Identifier. In the case of a Get expression, this isn't true anyway.
2020-10-17 Added `bitcastAs' operator to perform unsafe bitcasts such as changing the type of a pointer.
    This allows an implementation of something like an interface by casting a
    pointer to the concrete struct to a pointer to a vtable struct. So long as
    the vtable is the first element of the concrete struct, the field layout
    in memory is such that making member function calls through the casted
    pointer will work as expected.
    Also, the instance of the concrete struct needs to have a vtable properly
2020-10-19 can cast from pointer-to-struct to trait object
2020-10-22 Fix bug where `const Range' cannot be used to subscript a string.
2020-10-22 Fix bug where const self pointer in trait declaration caused a compiler crash.
2020-10-23 Compilation of a literal string expression issues a long list of STORE-IMMEDIATE instructions directly to the destination addresses.
2020-10-24 Extract creation of IR instruction listing to new CrackleInstructionListingMaker class.
2020-10-24 The COPY IR instruction uses a loop when the count is large.
    This prevents the instruction from generating more than 92 bytes of code,
    regardless of the count. When the count is smaller than the threshold, the
    copy loop is completely unrolled.
2020-10-24 The ENTER instruction generates a call to a new procedure. This reduces the amount of code emitted.
2020-10-24 The RET instruction generates a call to a new procedure. This reduces the amount of code emitted.
2020-10-25 Add new operators to the lexer: &&, ||, !, ^, ~, <<, and >>
2020-10-26 Fix bug which prevents a trait from being stored in a struct member.
2020-10-28 Begin work on an optimizer for Crackle IR code.
    The compiler generates some really unfortunate code. It can be greatly
    improved by rewriting instructions based on what can be statically
    determined about the contents of memory. For example, we know the value of
    memory when a STORE-IMMEDIATE is issued. We can then use this information
    to determine the source and destination addresses in indirect copies and
    replace them with direct copy equivalents.
2020-10-28 Dead code elimination in IR basic blocks.
2020-10-31 Optimize compiled programs by propagating constants in assembly code.
    Immediate values which are loaded into registers and memory can be tracked
    across a basic block. We can skip instructions which would have no effect
    such as LI X, Something when we already know that X contains Something.
    Similar tracking can be done for the contents of RAM.
    Instructions can be rewritten from MOV to LI when we can statically
    determine the value that will be assigned. The benefits of this change will
2020-11-01 Rewrite dead store elimination to fix bugs uncovered by other work.
2020-11-02 Add comments to mark a couple of nasty hacks.
2020-11-03 Fix bug which broke symbol table debug info.
